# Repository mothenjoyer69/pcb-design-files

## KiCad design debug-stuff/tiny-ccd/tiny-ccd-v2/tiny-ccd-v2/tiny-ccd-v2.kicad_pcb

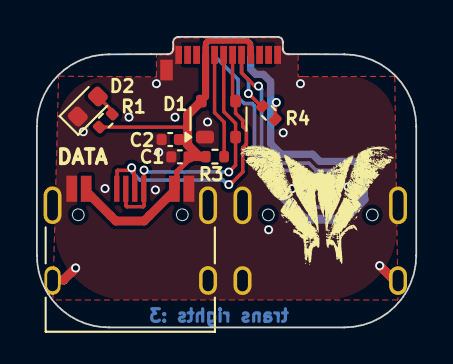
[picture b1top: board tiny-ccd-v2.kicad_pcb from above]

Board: 2 copper layers, 21.1 x 16.1 mm, 10 parts (1 on the bottom side), 9 nets.

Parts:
C1, C2: 10u; C_0402_1005Metric
D1: PRTR5V0U2X; SOT-143
D2: PINK_ACTIVITY; LED_0603_1608Metric
J1: USB-C_PLUG; USB_C_Plug_Molex_105444
J2: USB-C_DEBUG; USB_C_Receptacle_HRO_TYPE-C-31-M-12
J3: USB-C_DATA; USB_C_Receptacle_HRO_TYPE-C-31-M-12
R1: 1.5k; R_0402_1005Metric
R3: 22k; R_0402_1005Metric
R4: 56k; R_0402_1005Metric

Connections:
CC1: J1.A5 (CC1), R3.1
CC2: J1.B5 (CC2), R4.1
DBG_N: J1.A8 (SBU2), J3.A7 (D-), J3.B7 (D-)
DBG_P: J1.B8 (SBU1), J3.A6 (D+), J3.B6 (D+)
GND: C1.2, C2.1, D1.1 (GND), D2.1 (K), J1.A1 (GND), J1.A12 (GND), J1.B1 (GND), J1.B12 (GND), J1.S1 (SHIELD), J2.A1 (GND), J2.A12 (GND), J2.B1 (GND), J2.B12 (GND), J2.S1 (SHIELD), J3.A1 (GND), J3.A12 (GND), J3.B1 (GND), J3.B12 (GND), J3.S1 (SHIELD)
unnamed: D2.2 (A), R1.1
USB_N: D1.3 (I/O2), J1.A7 (D-), J2.A7 (D-), J2.B7 (D-)
USB_P: D1.2 (I/O1), J1.A6 (D+), J2.A6 (D+), J2.B6 (D+)
VBUS: C1.1, C2.2, D1.4 (VCC), J1.A4 (VBUS), J1.A9 (VBUS), J1.B4 (VBUS), J1.B9 (VBUS), J2.A4 (VBUS), J2.A9 (VBUS), J2.B4 (VBUS), J2.B9 (VBUS), J3.A4 (VBUS), J3.A9 (VBUS), J3.B4 (VBUS), J3.B9 (VBUS), R1.2, R3.2, R4.2

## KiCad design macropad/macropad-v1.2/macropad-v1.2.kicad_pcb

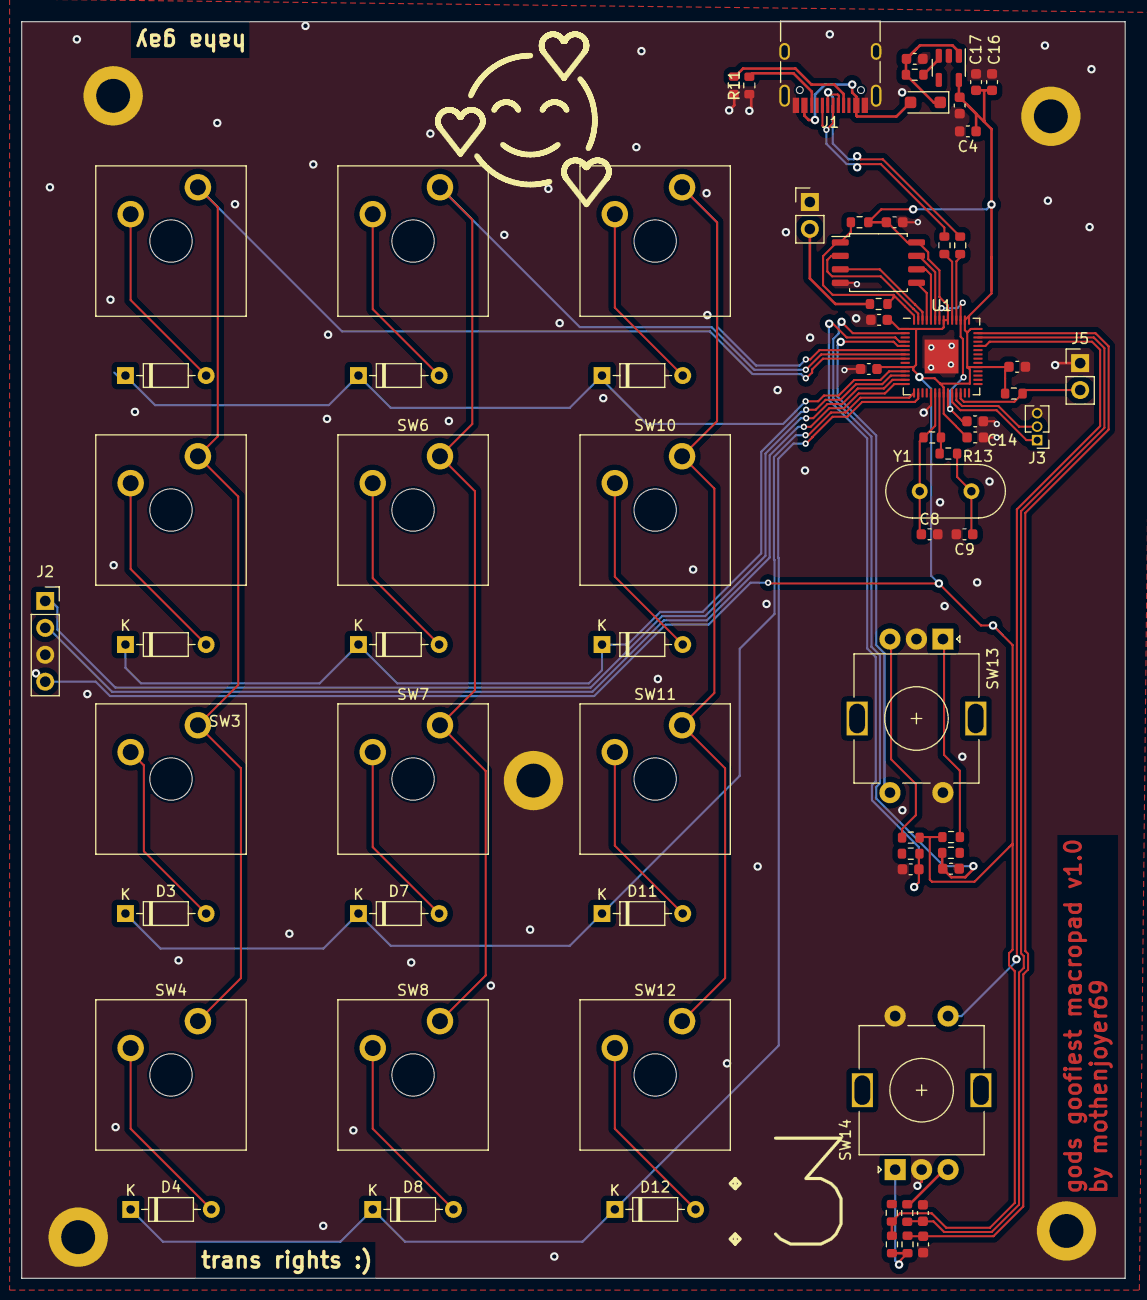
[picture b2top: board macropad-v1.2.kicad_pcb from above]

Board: 2 copper layers, 104.2 x 118.7 mm, 71 parts (0 on the bottom side), 56 nets.

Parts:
C1, C2, C10, C11: 0.01uF; C_0603_1608Metric
C3, C4, C6, C7, C12, C13, C14, C15, C16, C17: 1uF; C_0603_1608Metric
C5: 0.1uF; C_0603_1608Metric
C8, C9: 27pF; C_0603_1608Metric
D1, D2, D3, D4, D5, D6, D7, D8, D9, D10, D11, D12: 1N4148; D_DO-35_SOD27_P7.62mm_Horizontal
D14: MBR1020VL; D_SOD-123F
J1: USB_C_Receptacle_USB2.0; USB_C_Receptacle_HRO_TYPE-C-31-M-12
J2: OLED; PinSocket_1x04_P2.54mm_Vertical
J3: debug; PinHeader_1x03_P1.27mm_Vertical
J4: Boot pins; PinHeader_1x02_P2.54mm_Vertical
J5: Reset; PinHeader_1x02_P2.54mm_Vertical
R1, R2, R3, R4, R5, R8, R9, R12, R15, R16, R17: 10k; R_0603_1608Metric
R6, R7: 27; R_0603_1608Metric
R10, R11: 5k1; R_0603_1608Metric
R13, R18: 1k; R_0603_1608Metric
R14: DNP; R_0603_1608Metric
SW1, SW2, SW3, SW4, SW5, SW6, SW7, SW8, SW9, SW10, SW11, SW12: SW_Push; SW_Cherry_MX_Plate
SW13: RotaryEncoder_Switch_LEFT; RotaryEncoder_Alps_EC11E-Switch_Vertical_H20mm
SW14: RotaryEncoder_Switch_RIGHT; RotaryEncoder_Alps_EC11E-Switch_Vertical_H20mm
U1: RP2040; QFN-56-1EP_7x7mm_P0.4mm_EP3.2x3.2mm
U2: W25Q128JVS; SOIC-8_5.23x5.23mm_P1.27mm
U3: AP2112K-3.3; SOT-23-5
Y1: 12MHz; Crystal_HC49-U_Vertical

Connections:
+1V1: C3.1, U1.23 (DVDD), U1.45 (VREG_VOUT), U1.50 (DVDD)
+3.3V: C4.1, C5.1, C7.2, C12.1, C13.1, C14.1, C15.1, C16.1, C17.1, J2.4, R1.1, R2.1, R5.1, R8.2, R9.1, R15.1, U1.1 (IOVDD), U1.10 (IOVDD), U1.22 (IOVDD), U1.33 (IOVDD), U1.42 (IOVDD), U1.43 (ADC_AVDD), U1.44 (VREG_IN), U1.48 (USB_VDD), U1.49 (IOVDD), U2.8 (VCC), U3.5 (VOUT)
/BOOT_MODE: J4.2, R18.1
/C1: SW1.2, SW2.2, SW3.2, SW4.2, U1.8 (GPIO6)
/C2: SW5.2, SW6.2, SW7.2, SW8.2, U1.7 (GPIO5)
/C3: SW9.2, SW10.2, SW11.2, SW12.2, U1.6 (GPIO4)
/OLED_SCK: J2.2, U1.14 (GPIO11)
/OLED_SDA: J2.1, U1.13 (GPIO10)
/QSPI_CS: R8.1, R18.2, U1.56 (QSPI_SS), U2.1 (~CS)
/QSPI_SCK: U1.52 (QSPI_SCLK), U2.6 (CLK)
/QSPI_SD0: U1.53 (QSPI_SD0), U2.5 (DI(IO0))
/QSPI_SD1: U1.55 (QSPI_SD1), U2.2 (DO(IO1))
/QSPI_SD2: U1.54 (QSPI_SD2), U2.3 (IO2)
/QSPI_SD3: U1.51 (QSPI_SD3), U2.7 (IO3)
/R1: D1.1 (K), D5.1 (K), D9.1 (K), U1.11 (GPIO8)
/R2: D2.1 (K), D6.1 (K), D10.1 (K), U1.12 (GPIO9)
/R3: D3.1 (K), D7.1 (K), D11.1 (K), U1.15 (GPIO12)
/R4: D4.1 (K), D8.1 (K), D12.1 (K), U1.16 (GPIO13)
/ROT_AL: C1.2, R3.1, U1.2 (GPIO0)
/ROT_AR: C10.2, R16.1, U1.41 (GPIO29_ADC3)
/ROT_BL: C2.2, R4.2, U1.4 (GPIO2)
/ROT_BR: C11.2, R17.2, U1.40 (GPIO28_ADC2)
/ROT_S1L: SW13.S1, U1.5 (GPIO3)
/ROT_S1R: SW14.S1, U1.38 (GPIO26_ADC0)
/RUN: J5.2, R5.2, U1.26 (RUN)
/SWCLK: J3.1, U1.24 (SWCLK)
/SWD: J3.2, U1.25 (SWD)
/USB_N: J1.A7 (D-), J1.B7 (D-), R7.2
/USB_P: J1.A6 (D+), J1.B6 (D+), R6.1
/XIN: C8.1, R14.1, U1.20 (XIN), Y1.1
/XOUT: R13.1, R14.2, U1.21 (XOUT)
GND: C1.1, C2.1, C3.2, C4.2, C5.2, C6.1, C7.1, C8.2, C9.2, C10.1, C11.1, C12.2, C13.2, C14.2, C15.2, C16.2, C17.2, J1.A1 (GND), J1.A12 (GND), J1.B1 (GND), J1.B12 (GND), J1.S1 (SHIELD), J2.3, J3.3, J4.1, J5.1, R10.1, R11.1, SW13.C, SW13.S2, SW14.C, SW14.S2, U1.19 (TESTEN), U1.57 (GND), U2.4 (GND), U3.2 (GND)
unnamed: C9.1, R13.2, Y1.2
unnamed: D1.2 (A), SW1.1
unnamed: D2.2 (A), SW2.1
unnamed: D3.2 (A), SW3.1
unnamed: D4.2 (A), SW4.1
unnamed: D5.2 (A), SW5.1
unnamed: D6.2 (A), SW6.1
unnamed: D7.2 (A), SW7.1
unnamed: D8.2 (A), SW8.1
unnamed: D9.2 (A), SW9.1
unnamed: D10.2 (A), SW10.1
unnamed: D11.2 (A), SW11.1
unnamed: D12.2 (A), SW12.1
unnamed: D14.2 (A), J1.A4 (VBUS), J1.A9 (VBUS), J1.B4 (VBUS), J1.B9 (VBUS)
unnamed: C6.2, D14.1 (K), R12.2, U3.1 (VIN)
unnamed: J1.A5 (CC1), R10.2
unnamed: J1.B5 (CC2), R11.2
unnamed: R1.2, R4.1, SW13.B
unnamed: R2.2, R3.2, SW13.A
unnamed: R15.2, R16.2, SW14.A
unnamed: R9.2, R17.1, SW14.B
unnamed: R7.1, U1.46 (USB_DM)
unnamed: R6.2, U1.47 (USB_DP)
unnamed: R12.1, U3.3 (EN)

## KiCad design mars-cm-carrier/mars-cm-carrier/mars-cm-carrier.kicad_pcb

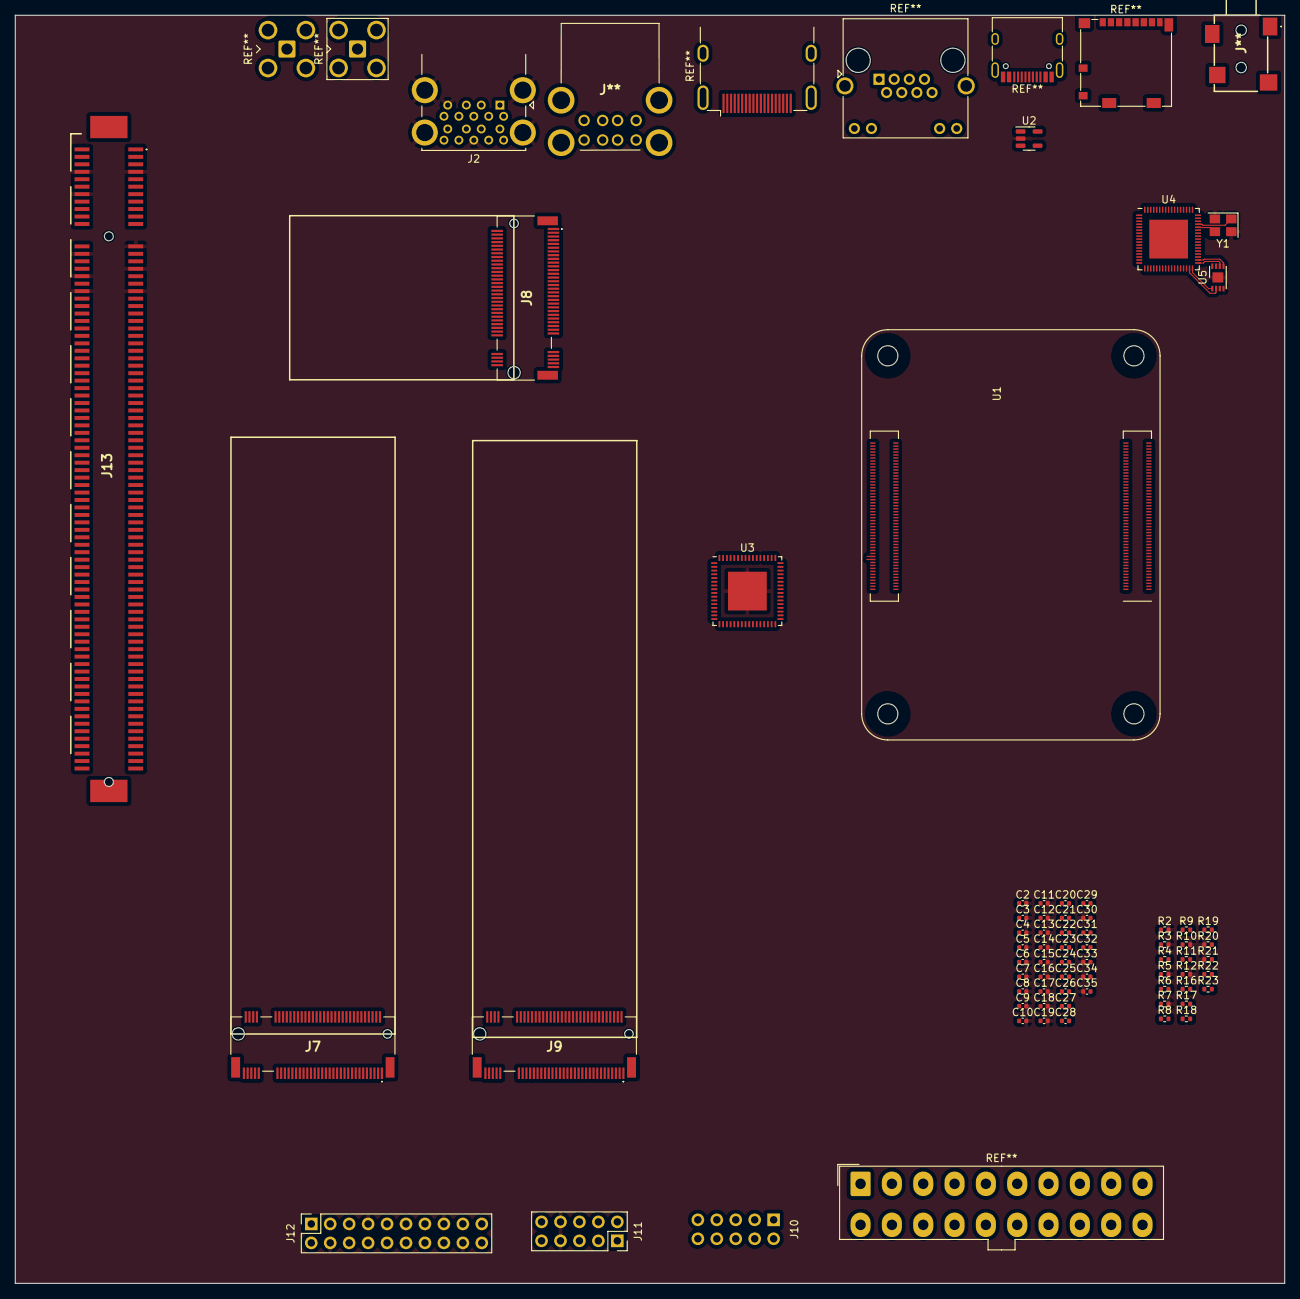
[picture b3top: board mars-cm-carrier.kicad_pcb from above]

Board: 6 copper layers, 170.2 x 170.0 mm, 69 parts (1 on the bottom side), 104 nets.

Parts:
C2, C3, C4, C5, C6, C7, C8, C9, C10, C11, C12, C13, C14, C15, C16, C17, C18, C19, C20, C21, C22, C23, C24, C25, C26, C27, C28, C29, C31, C32, C35: 100nF; C_0402_1005Metric
C30: 1uF; C_0402_1005Metric
C33, C34: 18pF; C_0402_1005Metric
J2: USB3_A_Stacked; USB3_A_Molex_48406-0001_Horizontal_Stacked
J7, J9: Bus_M.2_Socket_M; MDT275M02001
J8: Bus_M.2_Socket_ECHANGEFOOTPRINT; MDT275M02001
J10: FRONT_PANEL_IO; PinSocket_2x05_P2.54mm_Vertical
J11: USB2_FRONT_PANEL; PinSocket_2x05_P2.54mm_Vertical
J12: Conn_02x10_Counter_Clockwise; PinSocket_2x10_P2.54mm_Vertical
J13: 10018783-11200TLF; 10146070113Y0LF
J**: SJ22524ASMTTR
J**#2: 8964300890000000
R2, R3, R5, R7: 1K; R_0402_1005Metric
R4, R6, R8, R9, R11, R16, R17, R19, R23: 10K; R_0402_1005Metric
R10, R12: 12.1K; R_0402_1005Metric
R18: DNP; R_0402_1005Metric
R20: 4.7K; R_0402_1005Metric
R21: 6.04K; R_0402_1005Metric
R22: 15K; R_0402_1005Metric
U1: Compute_Module_4_Connectors; Raspberry-Pi-4-Compute-Module
U2: RT9742BNGJ5F; TSOT-23-5
U3: ASM1184; QFN-64-1EP_9x9mm_P0.5mm_EP5.2x5.2mm
U4: VL805; QFN-68-1EP_8x8mm_P0.4mm_EP5.2x5.2mm
U5: W25Q32JVZP; DFN-8-1EP_3x2mm_P0.5mm_EP1.36x1.46mm
Y1: 25Mhz; Crystal_SMD_3225-4Pin_3.2x2.5mm

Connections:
+1V1: U4.3 (VCCA10SSRX34), U4.9 (VDD), U4.12 (VCCA10SSRX34), U4.29 (VDD), U4.45 (VDD), U4.54 (VCCA10SSRX12), U4.60 (VDD), U4.63 (VCCA10SSRX12)
+1V2: C2.1, C3.1, C5.1, C6.1, C8.1, C9.1, C11.1, C12.1, C14.1, C15.1, C17.1, C18.1, U3.9 (1V2), U3.15 (1V2), U3.17 (1V2), U3.20 (1V2), U3.26 (1V2), U3.29 (1V2), U3.37 (1V2), U3.43 (1V2), U3.48 (1V2), U3.50 (1V2), U3.61 (1V2), U3.64 (1V2)
+3V3: C4.1, C7.1, C10.1, C13.1, C16.1, C19.1, C35.2, J7.2 (3.3V), J7.4 (3.3V), J7.12 (3.3V), J7.14 (3.3V), J7.16 (3.3V), J7.18 (3.3V), J7.70 (3.3V), J7.72 (3.3V), J7.74 (3.3V), J8.2 (3.3V), J8.4 (3.3V), J8.72 (3.3V), J8.74 (3.3V), J9.2 (3.3V), J9.4 (3.3V), J9.12 (3.3V), J9.14 (3.3V), J9.16 (3.3V), J9.18 (3.3V), J9.70 (3.3V), J9.72 (3.3V), J9.74 (3.3V), R4.1, R6.1, R8.1, R9.1, R11.1, R16.2, R17.2, R18.2, R19.2, R22.1, R23.1, U2.5 (VIN), U3.1 (3V_AUX), U3.10 (3V3), U3.21 (3V3), U3.32 (3V3), U3.38 (3V3), U3.56 (3V3), U4.6 (VCCA33SS34), U4.15 (VCCA33SS34), U4.23 (VCCA33PEX), U4.32 (VSUS33), U4.46 (VSUS33), U4.49 (VCCA33SSM), U4.57 (VCCA33SS12), U4.66 (VCCA33SS12), U5.7 (IO3), U5.8 (VCC)
+5V: J2.1 (VBUS1), J2.10 (VBUS2), J12.10, J12.12, U1.77 (+5V), U1.79 (+5V), U1.81 (+5V), U1.83 (+5V), U1.85 (+5V), U1.87 (+5V)
/5V: J10.9, J11.1, J11.2
/+3.3v: J13.A5 (TCK), J13.A6 (TDI), J13.A8 (TMS), J13.A9 (+3.3V), J13.A10 (+3.3V), J13.B8 (+3.3v), J13.B9 (nTRST), J13.B10 (+3.3vAUX)
/+12v: J13.A2 (+12V), J13.A3 (+12V), J13.B1 (+12v), J13.B2 (+12v), J13.B3 (+12v)
/FPUSB_D+: J11.5, J11.6
/FPUSB_D-: J11.3, J11.4
/PCIe1_CLK_N: J7.53 (REFCLKn), U3.19 (REFCLKN_1)
/PCIe1_CLK_P: J7.55 (REFCLKp), U3.18 (REFCLKP_1)
/PCIe1_RX_N: J7.41 (PERn0/SATA-B+), U3.14 (RXN_1)
/PCIe1_RX_P: J7.43 (PERp0/SATA-B-), U3.13 (RXP_1)
/PCIe1_TX_N: C21.1, J7.47 (PETn0/SATA-A-)
/PCIe1_TX_P: C20.1, J7.49 (PETp0/SATA-A+)
/PCIe2_CLK_N: J8.49 (REFCLKn0), U3.28 (REFCLKN_2)
/PCIe2_CLK_P: J8.47 (REFCLKp0), U3.27 (REFCLKP_2)
/PCIe2_RX_N: J8.43 (PERn0), U3.25 (RXN_2)
/PCIe2_RX_P: J8.41 (PERp0), U3.24 (RXP_2)
/PCIe2_TX_N: C23.1, J8.37 (PETn0)
/PCIe2_TX_P: C22.1, J8.35 (PETp0)
/PCIe3_CLK_N: J9.53 (REFCLKn), U3.45 (REFCLKN_3)
/PCIe3_CLK_P: J9.55 (REFCLKp), U3.44 (REFCLKP_3)
/PCIe3_RX_N: J9.41 (PERn0/SATA-B+), U3.42 (RXN_3)
/PCIe3_RX_P: J9.43 (PERp0/SATA-B-), U3.41 (RXP_3)
/PCIe3_TX_N: C25.1, J9.47 (PETn0/SATA-A-)
/PCIe3_TX_P: C24.1, J9.49 (PETp0/SATA-A+)
/PCIe4_CLK_N: U3.63 (REFCLKN_4), U4.22 (PE_CLKN)
/PCIe4_CLK_P: U3.62 (REFCLKP_4), U4.21 (PE_CLKP)
/PCIe4_RX_N: C31.1, U3.60 (RXN_4)
/PCIe4_RX_P: C32.1, U3.59 (RXP_4)
/PCIe4_TX_N: C27.1, U4.27 (PE_RXP)
/PCIe4_TX_P: C26.1, U4.28 (PE_RXN)
/PCIe_CLK_REQ: C30.2, R16.1, R17.1, R18.1, R19.1, R20.2, U4.18 (~SMI), U4.20 (~PE_WAKE), U4.30 (~PE_CLKREQ), U4.31 (~PONRST), U4.51 (TESTEN)
/PCIe_IN_CLK_N: U1.112 (PCIe_CLK_N), U3.47 (REFCLKN_IN)
/PCIe_IN_CLK_P: U1.110 (PCIe_CLK_P), U3.46 (REFCLKP_IN)
/PCIe_IN_RX_N: C29.1, U1.118 (PCIe_RX_N)
/PCIe_IN_RX_P: C28.1, U1.116 (PCIe_RX_P)
/PCIe_IN_TX_N: U1.124 (PCIe_TX_N), U3.52 (RXN_IN)
/PCIe_IN_TX_P: U1.122 (PCIe_TX_P), U3.51 (RXP_IN)
/PCIe_RST: U3.3 (RES_IN), U4.19 (~PE_RST)
/PCIe_RST_M2: J7.50 (~PERST), J8.52 (~PERST0), J9.50 (~PERST), U3.2 (RES_OUT)
/USB2_D1+: J2.3 (D1+), U4.58 (USB2D1+)
/USB2_D1-: J2.2 (D1-), U4.59 (USB2D1-)
/USB2_D2+: J2.12 (D2+), U4.67 (USB2D2+)
/USB2_D2-: J2.11 (D2-), U4.68 (USB2D2-)
/USB2_D3+: J12.2, U4.7 (USB2D3+)
/USB2_D3-: J12.3, U4.8 (USB2D3-)
/USB2_D4+: J12.20, U4.16 (USB2D4+)
/USB2_D4-: J12.19, U4.17 (USB2D4-)
/USB3_RX1+: J2.9 (SSTX1+), U4.55 (SSRX1+)
/USB3_RX1-: J2.8 (SSTX1-), U4.56 (SSRX1-)
/USB3_RX2+: J2.18 (SSTX2+), U4.64 (SSRX2+)
/USB3_RX2-: J2.17 (SSTX2-), U4.65 (SSRX2-)
/USB3_RX3+: J12.8, U4.4 (SSRX3+)
/USB3_RX3-: J12.9, U4.5 (SSRX3-)
/USB3_RX4+: J12.14, U4.13 (SSRX4+)
/USB3_RX4-: J12.13, U4.14 (SSRX4-)
/USB3_TX1+: J2.6 (SSRX1+), U4.52 (SSTX1+)
/USB3_TX1-: J2.5 (SSRX1-), U4.53 (SSTX1-)
/USB3_TX2+: J2.15 (SSRX2+), U4.61 (SSTX2+)
/USB3_TX2-: J2.14 (SSRX2-), U4.62 (SSTX2-)
/USB3_TX3+: J12.5, U4.1 (SSTX3+)
/USB3_TX4+: J12.17, U4.10 (SSTX4+)
/USB3_TX4-: J12.16, U4.11 (SSTX4-)
/USB_TX3-: J12.6, U4.2 (SSTX3-)
GND: C2.2, C3.2, C4.2, C5.2, C6.2, C7.2, C8.2, C9.2, C10.2, C11.2, C12.2, C13.2, C14.2, C15.2, C16.2, C17.2, C18.2, C19.2, C30.1, C33.1, C34.1, C35.1, J2.4 (GND1), J2.7 (DRAIN1), J2.13 (GND2), J2.16 (DRAIN2), J2.19 (SHIELD), J11.7, J11.8, J12.4, J12.7, J12.15, J12.18, J13.A4 (GND), J13.A12 (GND), J13.A15 (GND), J13.A18 (GND), J13.B4 (GND), J13.B7 (GND), J13.B13 (GND), J13.B16 (GND), J13.B18 (GND), R2.2, R3.2, R5.2, R7.2, R10.2, R12.2, R20.1, R21.1, U1.1 (GND), U1.2 (GND), U1.7 (GND), U1.8 (GND), U1.13 (GND), U1.14 (GND), U1.22 (GND), U1.23 (GND), U1.32 (GND), U1.33 (GND), U1.42 (GND), U1.43 (GND), U1.52 (GND), U1.53 (GND), U1.59 (GND), U1.60 (GND), U1.65 (GND), U1.66 (GND), U1.71 (GND), U1.74 (GND), U1.98 (GND), U2.2 (GND), U3.53 (GND), U3.65 (GND), U4.69 (GND), U5.4 (GND), U5.9 (EP), Y1.2, Y1.4
unnamed: J7.1 (GND), J7.3 (GND), J7.9 (GND), J7.15 (GND), J7.21 (GND), J7.27 (GND), J7.33 (GND), J7.39 (GND), J7.45 (GND), J7.51 (GND), J7.57 (GND), J7.71 (GND), J7.73 (GND), J7.75 (GND)
unnamed: J8.1 (GND), J8.7 (GND), J8.18 (GND), J8.33 (GND), J8.39 (GND), J8.45 (GND), J8.51 (GND), J8.57 (GND), J8.69 (GND), J8.75 (GND)
unnamed: J9.1 (GND), J9.3 (GND), J9.9 (GND), J9.15 (GND), J9.21 (GND), J9.27 (GND), J9.33 (GND), J9.39 (GND), J9.45 (GND), J9.51 (GND), J9.57 (GND), J9.71 (GND), J9.73 (GND), J9.75 (GND)
unnamed: U1.107 (GND), U1.113 (GND), U1.119 (GND), U1.125 (GND), U1.131 (GND), U1.137 (GND), U1.155 (GND), U1.161 (GND), U1.167 (GND), U1.173 (GND), U1.179 (GND), U1.185 (GND), U1.191 (GND), U1.197 (GND)
unnamed: U1.108 (GND), U1.114 (GND), U1.120 (GND), U1.126 (GND), U1.132 (GND), U1.138 (GND), U1.144 (GND), U1.150 (GND), U1.156 (GND), U1.162 (GND), U1.168 (GND), U1.174 (GND), U1.180 (GND), U1.186 (GND), U1.192 (GND), U1.198 (GND)
unnamed: R11.2, U3.4 (GPIO_0)
unnamed: R4.2, U3.31 (GPIO_1)
unnamed: R3.1, U3.5 (GPIO_2)
unnamed: R9.2, U3.34 (GPIO_3)
unnamed: R2.1, U3.8 (GPIO_4)
unnamed: R6.2, U3.30 (GPIO_5)
unnamed: R5.1, U3.35 (GPIO_6)
unnamed: R8.2, U3.36 (GPIO_7)
unnamed: R10.1, U3.16 (REXT1)
unnamed: R12.1, U3.49 (REXT2)
unnamed: R7.1, U3.33 (TEST_EN)
unnamed: C21.2, U3.12 (TXN_1)
unnamed: C23.2, U3.23 (TXN_2)
unnamed: C25.2, U3.40 (TXN_3)
unnamed: C27.2, U3.58 (TXN_4)
unnamed: C29.2, U3.55 (TXN_IN)
unnamed: C20.2, U3.11 (TXP_1)
unnamed: C22.2, U3.22 (TXP_2)
unnamed: C24.2, U3.39 (TXP_3)
unnamed: C26.2, U3.57 (TXP_4)
unnamed: C28.2, U3.54 (TXP_IN)
unnamed: C32.2, U4.25 (PE_TXN)
unnamed: C31.2, U4.24 (PE_TXP)
unnamed: U4.35 (SPI_CLK), U5.6 (CLK)
unnamed: U4.34 (SPI_CS), U5.1 (~CS)
unnamed: U4.36 (SPI_DI), U5.5 (DI(IO0))
unnamed: U4.33 (SPI_DO), U5.2 (DO(IO1))
unnamed: R21.2, U4.50 (SSREXT)
unnamed: C34.2, U4.47 (XI), Y1.3
unnamed: C33.2, U4.48 (XO), Y1.1
unnamed: R22.2, U4.37 (~USBHOC4), U4.39 (~USBHOC3), U4.41 (~USBHOC2), U4.43 (~USBHOC1)
unnamed: R23.2, U5.3 (IO2)

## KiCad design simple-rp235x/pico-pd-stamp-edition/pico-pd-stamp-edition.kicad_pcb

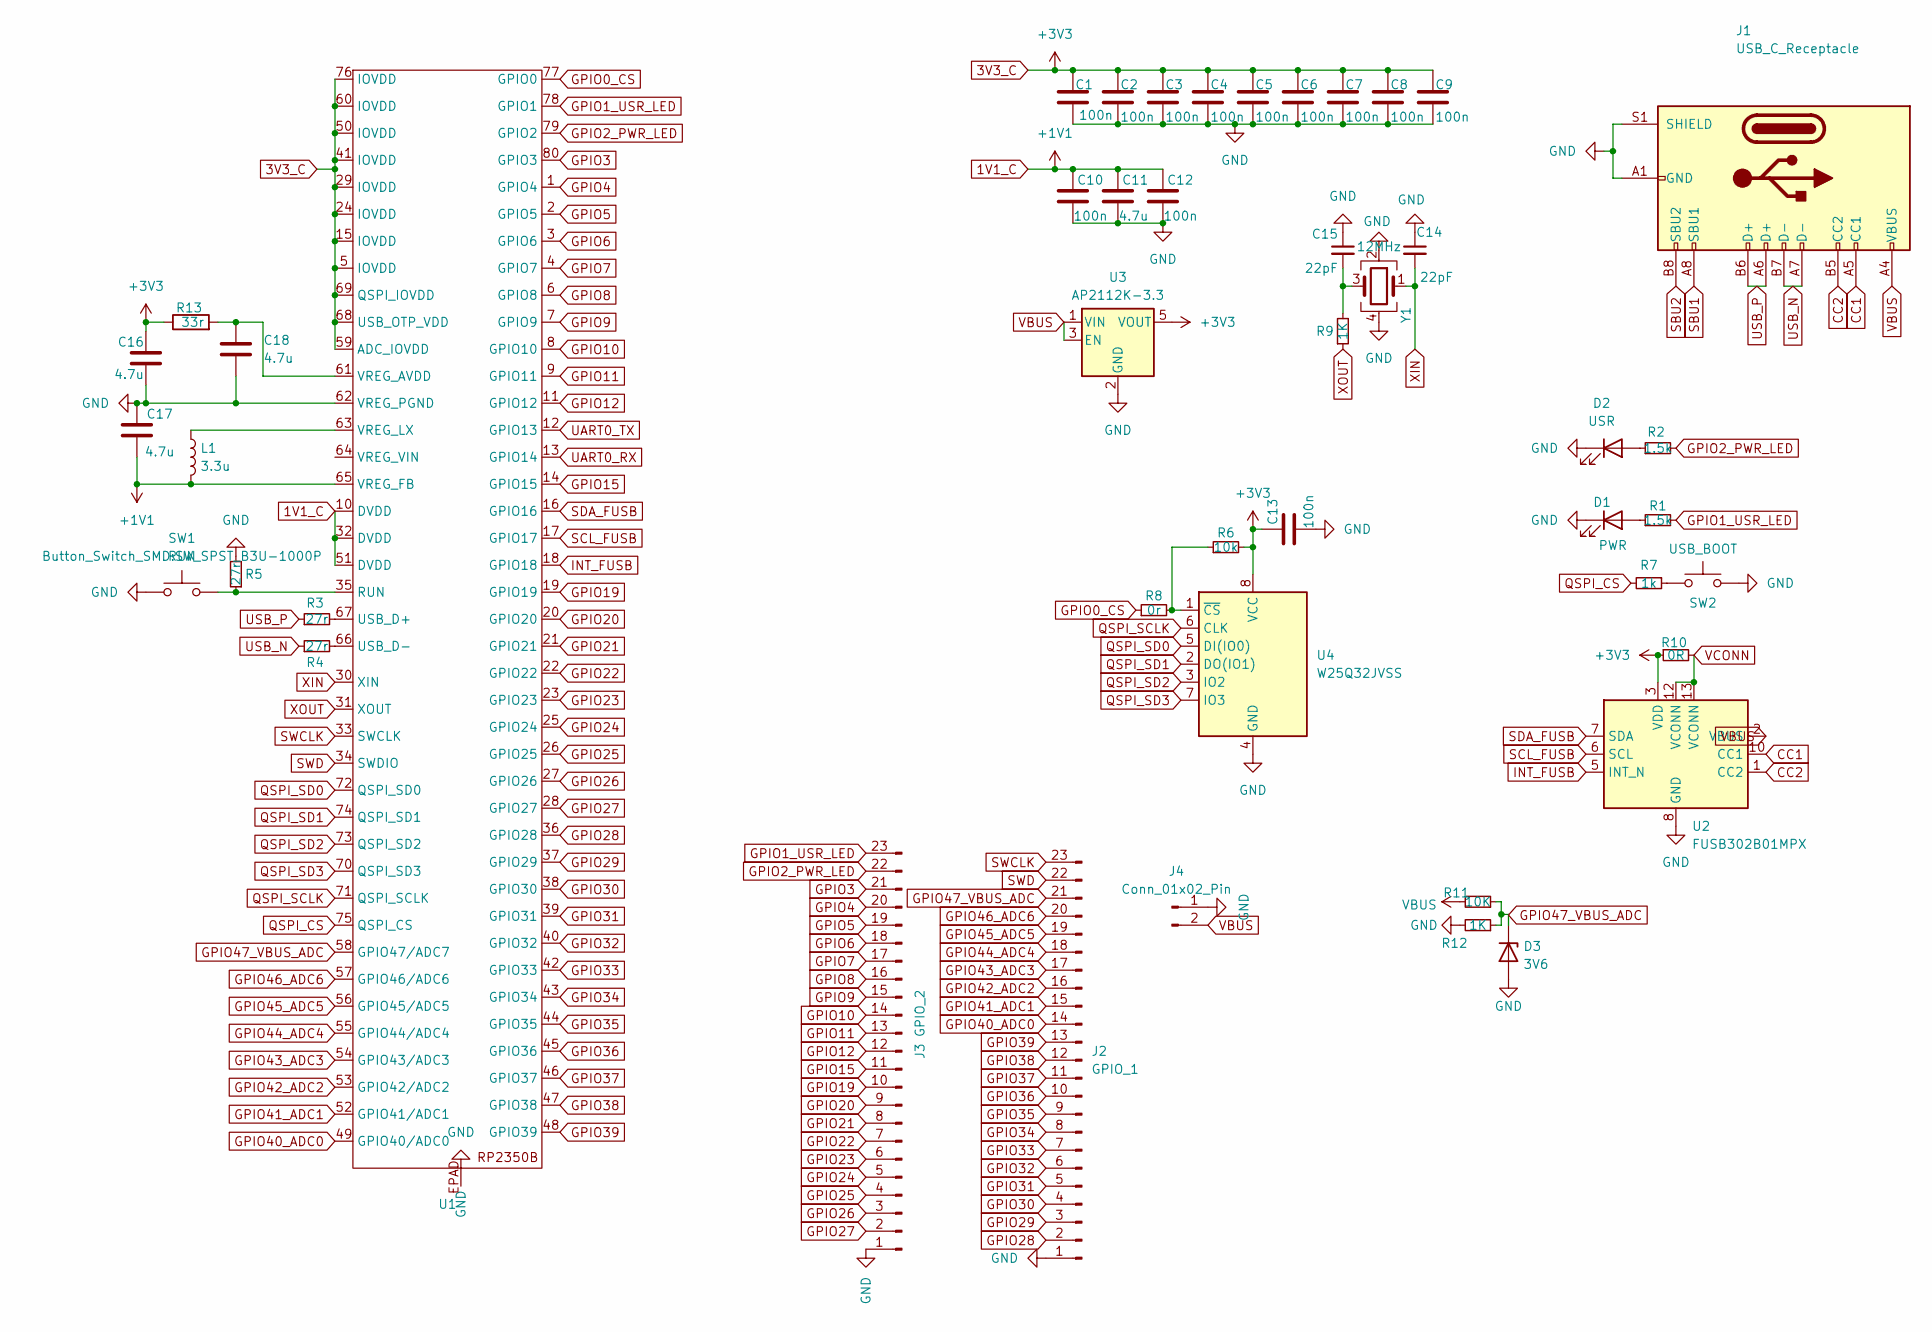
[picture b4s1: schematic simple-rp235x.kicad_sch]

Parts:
C1, C2, C3, C4, C5, C6, C7, C8, C9, C10, C12: 100n; C_0402_1005Metric
C11, C16, C17, C18: 4.7u; C_0402_1005Metric
C13: 100n; R_0402_1005Metric
C14, C15: 22pF; C_0603_1608Metric
D1: PWR; LED_0603_1608Metric
D2: USR; LED_0603_1608Metric
D3: 3V6; D_0805_2012Metric
J1: USB_C_Receptacle; USB_C_Receptacle_HRO_TYPE-C-31-M-12
J2: GPIO_1; PinSocket_1x23_P2.54mm_Vertical
J3: GPIO_2; PinSocket_1x23_P2.54mm_Vertical
J4: Conn_01x02_Pin; PinSocket_1x02_P2.54mm_Vertical
L1: 3.3u; L_0805_2012Metric
R1, R2: 1.5k; R_0402_1005Metric
R3, R4, R5: 27r; R_0402_1005Metric
R6: 10k; R_0402_1005Metric
R7: 1k; R_0402_1005Metric
R8: 0r; R_0402_1005Metric
R9, R12: 1K; R_0402_1005Metric
R10: 0R; R_0603_1608Metric
R11: 10K; R_0402_1005Metric
R13: 33r; R_0402_1005Metric
SW1: RUN; SW_SPST_B3U-1000P
SW2: USB_BOOT; SW_SPST_B3U-1000P
U1: QFN-80_EP_10.573x10.573_Pitch0.4mm
U2: FUSB302B01MPX; WQFN-14-1EP_2.5x2.5mm_P0.5mm_EP1.45x1.45mm
U3: AP2112K-3.3; SOT-23-5
U4: W25Q32JVSS; SOIC-8_5.23x5.23mm_P1.27mm
Y1: 12MHz; Crystal_SMD_3225-4Pin_3.2x2.5mm

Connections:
1V1_C: C10.1, C11.1, C12.1, C17.2, L1.2, U1.10 (DVDD), U1.32 (DVDD), U1.51 (DVDD), U1.65 (VREG_FB)
3V3_C: C1.1, C2.1, C3.1, C4.1, C5.1, C6.1, C7.1, C8.1, C9.1, C13.1, C16.1, R6.2, R10.1, R13.1, U1.5 (IOVDD), U1.15 (IOVDD), U1.24 (IOVDD), U1.29 (IOVDD), U1.41 (IOVDD), U1.50 (IOVDD), U1.59 (ADC_IOVDD), U1.60 (IOVDD), U1.68 (USB_OTP_VDD), U1.69 (QSPI_IOVDD), U1.76 (IOVDD), U2.3 (VDD), U2.4 (VDD), U3.5 (VOUT), U4.8 (VCC)
CC1: J1.A5 (CC1), U2.10 (CC1), U2.11 (CC1)
CC2: J1.B5 (CC2), U2.1 (CC2), U2.14 (CC2)
GND: C1.2, C2.2, C3.2, C4.2, C5.2, C6.2, C7.2, C8.2, C9.2, C10.2, C11.2, C12.2, C13.2, C14.1, C15.1, C16.2, C17.1, C18.2, D1.1 (K), D2.1 (K), D3.2 (A), J1.A1 (GND), J1.A12 (GND), J1.B1 (GND), J1.B12 (GND), J1.S1 (SHIELD), J2.1, J3.1, J4.1, R5.2, R12.2, SW1.1, SW2.2, U1.62 (VREG_PGND), U1.EPAD (GND), U2.8 (GND), U2.9 (GND), U2.15 (GND), U3.2 (GND), U4.4 (GND), Y1.2, Y1.4
GPIO0_CS: R8.1, U1.77 (GPIO0)
GPIO1_USR_LED: J3.23, R1.2, U1.78 (GPIO1)
GPIO2_PWR_LED: J3.22, R2.2, U1.79 (GPIO2)
GPIO3: J3.21, U1.80 (GPIO3)
GPIO4: J3.20, U1.1 (GPIO4)
GPIO5: J3.19, U1.2 (GPIO5)
GPIO6: J3.18, U1.3 (GPIO6)
GPIO7: J3.17, U1.4 (GPIO7)
GPIO8: J3.16, U1.6 (GPIO8)
GPIO9: J3.15, U1.7 (GPIO9)
GPIO10: J3.14, U1.8 (GPIO10)
GPIO11: J3.13, U1.9 (GPIO11)
GPIO12: J3.12, U1.11 (GPIO12)
GPIO15: J3.11, U1.14 (GPIO15)
GPIO19: J3.10, U1.19 (GPIO19)
GPIO20: J3.9, U1.20 (GPIO20)
GPIO21: J3.8, U1.21 (GPIO21)
GPIO22: J3.7, U1.22 (GPIO22)
GPIO23: J3.6, U1.23 (GPIO23)
GPIO24: J3.5, U1.25 (GPIO24)
GPIO25: J3.4, U1.26 (GPIO25)
GPIO26: J3.3, U1.27 (GPIO26)
GPIO27: J3.2, U1.28 (GPIO27)
GPIO28: J2.2, U1.36 (GPIO28)
GPIO29: J2.3, U1.37 (GPIO29)
GPIO30: J2.4, U1.38 (GPIO30)
GPIO31: J2.5, U1.39 (GPIO31)
GPIO32: J2.6, U1.40 (GPIO32)
GPIO33: J2.7, U1.42 (GPIO33)
GPIO34: J2.8, U1.43 (GPIO34)
GPIO35: J2.9, U1.44 (GPIO35)
GPIO36: J2.10, U1.45 (GPIO36)
GPIO37: J2.11, U1.46 (GPIO37)
GPIO38: J2.12, U1.47 (GPIO38)
GPIO39: J2.13, U1.48 (GPIO39)
GPIO40_ADC0: J2.14, U1.49 (GPIO40/ADC0)
GPIO41_ADC1: J2.15, U1.52 (GPIO41/ADC1)
GPIO42_ADC2: J2.16, U1.53 (GPIO42/ADC2)
GPIO43_ADC3: J2.17, U1.54 (GPIO43/ADC3)
GPIO44_ADC4: J2.18, U1.55 (GPIO44/ADC4)
GPIO45_ADC5: J2.19, U1.56 (GPIO45/ADC5)
GPIO46_ADC6: J2.20, U1.57 (GPIO46/ADC6)
GPIO47_VBUS_ADC: D3.1 (K), J2.21, R11.1, R12.1, U1.58 (GPIO47/ADC7)
INT_FUSB: U1.18 (GPIO18), U2.5 (INT_N)
unnamed: C15.2, R9.2, Y1.3
unnamed: D1.2 (A), R1.1
unnamed: D2.2 (A), R2.1
unnamed: R7.1, SW2.1
unnamed: R5.1, SW1.2, U1.35 (RUN)
unnamed: R3.2, U1.67 (USB_D+)
unnamed: R4.2, U1.66 (USB_D-)
unnamed: C18.1, R13.2, U1.61 (VREG_AVDD)
unnamed: L1.1, U1.63 (VREG_LX)
unnamed: R6.1, R8.2, U4.1 (~CS)
QSPI_CS: R7.2, U1.75 (QSPI_CS)
QSPI_SCLK: U1.71 (QSPI_SCLK), U4.6 (CLK)
QSPI_SD0: U1.72 (QSPI_SD0), U4.5 (DI(IO0))
QSPI_SD1: U1.74 (QSPI_SD1), U4.2 (DO(IO1))
QSPI_SD2: U1.73 (QSPI_SD2), U4.3 (IO2)
QSPI_SD3: U1.70 (QSPI_SD3), U4.7 (IO3)
SBU1: J1.A8 (SBU1)
SBU2: J1.B8 (SBU2)
SCL_FUSB: U1.17 (GPIO17), U2.6 (SCL)
SDA_FUSB: U1.16 (GPIO16), U2.7 (SDA)
SWCLK: J2.23, U1.33 (SWCLK)
SWD: J2.22, U1.34 (SWDIO)
UART0_RX: U1.13 (GPIO14)
UART0_TX: U1.12 (GPIO13)
USB_N: J1.A7 (D-), J1.B7 (D-), R4.1
USB_P: J1.A6 (D+), J1.B6 (D+), R3.1
VBUS: J1.A4 (VBUS), J1.A9 (VBUS), J1.B4 (VBUS), J1.B9 (VBUS), J4.2, R11.2, U2.2 (VBUS), U3.1 (VIN), U3.3 (EN)
VCONN: R10.2, U2.12 (VCONN), U2.13 (VCONN)
XIN: C14.2, U1.30 (XIN), Y1.1
XOUT: R9.1, U1.31 (XOUT)

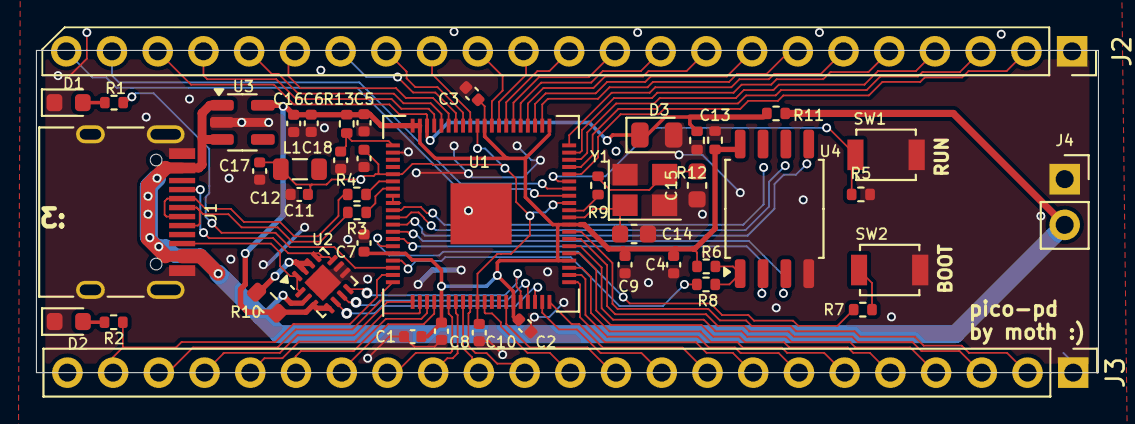
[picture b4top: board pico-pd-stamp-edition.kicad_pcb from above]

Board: 2 copper layers, 59.0 x 17.9 mm, 46 parts (0 on the bottom side), 75 nets.
